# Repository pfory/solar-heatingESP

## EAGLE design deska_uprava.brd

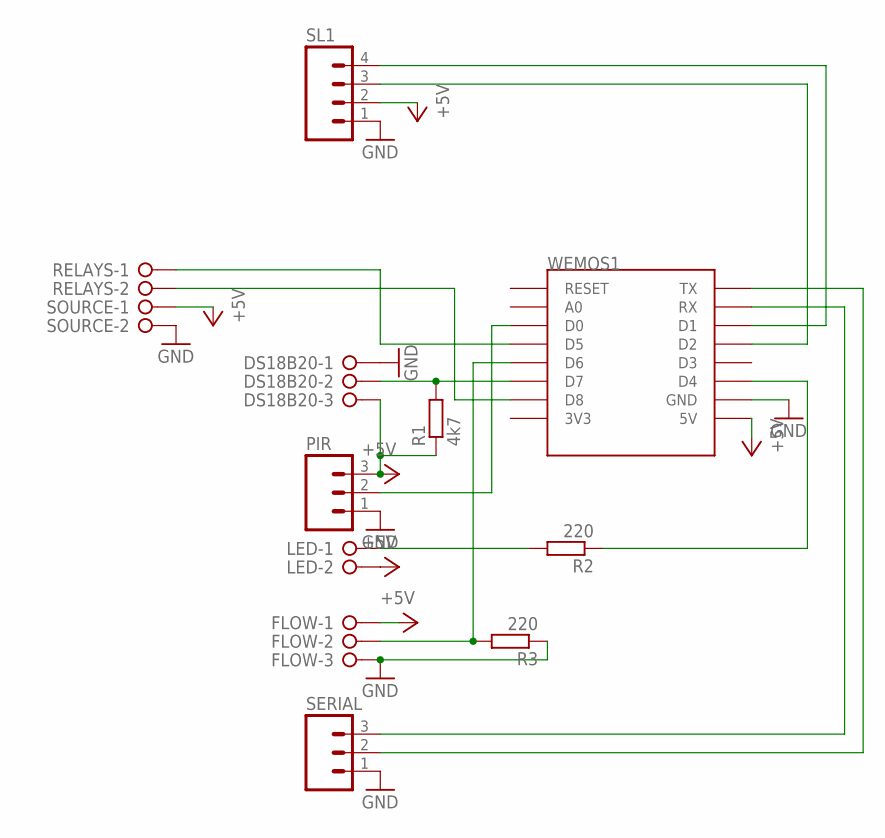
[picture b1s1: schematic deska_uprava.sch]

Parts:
DS18B20: W237-03P; W237-133
FLOW: W237-03P; W237-133
LED: W237-02P; W237-132
PIR: M03; 03P
R1: 4k7; 0207/10
R2, R3: 220; 0207/10
RELAYS: W237-02P; W237-132
SERIAL: M03; 03P
SL1: M04; 04P
SOURCE: W237-02P; W237-132
WEMOS1: WEMOS-D1-MINI

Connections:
+5V: DS18B20.3, FLOW.1, LED.2, PIR.3, R1.1, SL1.2, SOURCE.1, WEMOS1.5V
GND: DS18B20.1, FLOW.3, PIR.1, R3.1, SERIAL.1, SL1.1, SOURCE.2, WEMOS1.GND
unnamed: SERIAL.2, WEMOS1.TX
unnamed: SERIAL.3, WEMOS1.RX
unnamed: SL1.4, WEMOS1.D1
unnamed: SL1.3, WEMOS1.D2
unnamed: PIR.2, WEMOS1.D0
unnamed: R2.1, WEMOS1.D4
unnamed: RELAYS.1, WEMOS1.D5
unnamed: RELAYS.2, WEMOS1.D8
unnamed: DS18B20.2, R1.2, WEMOS1.D7
unnamed: FLOW.2, R3.2, WEMOS1.D6
unnamed: LED.1, R2.2

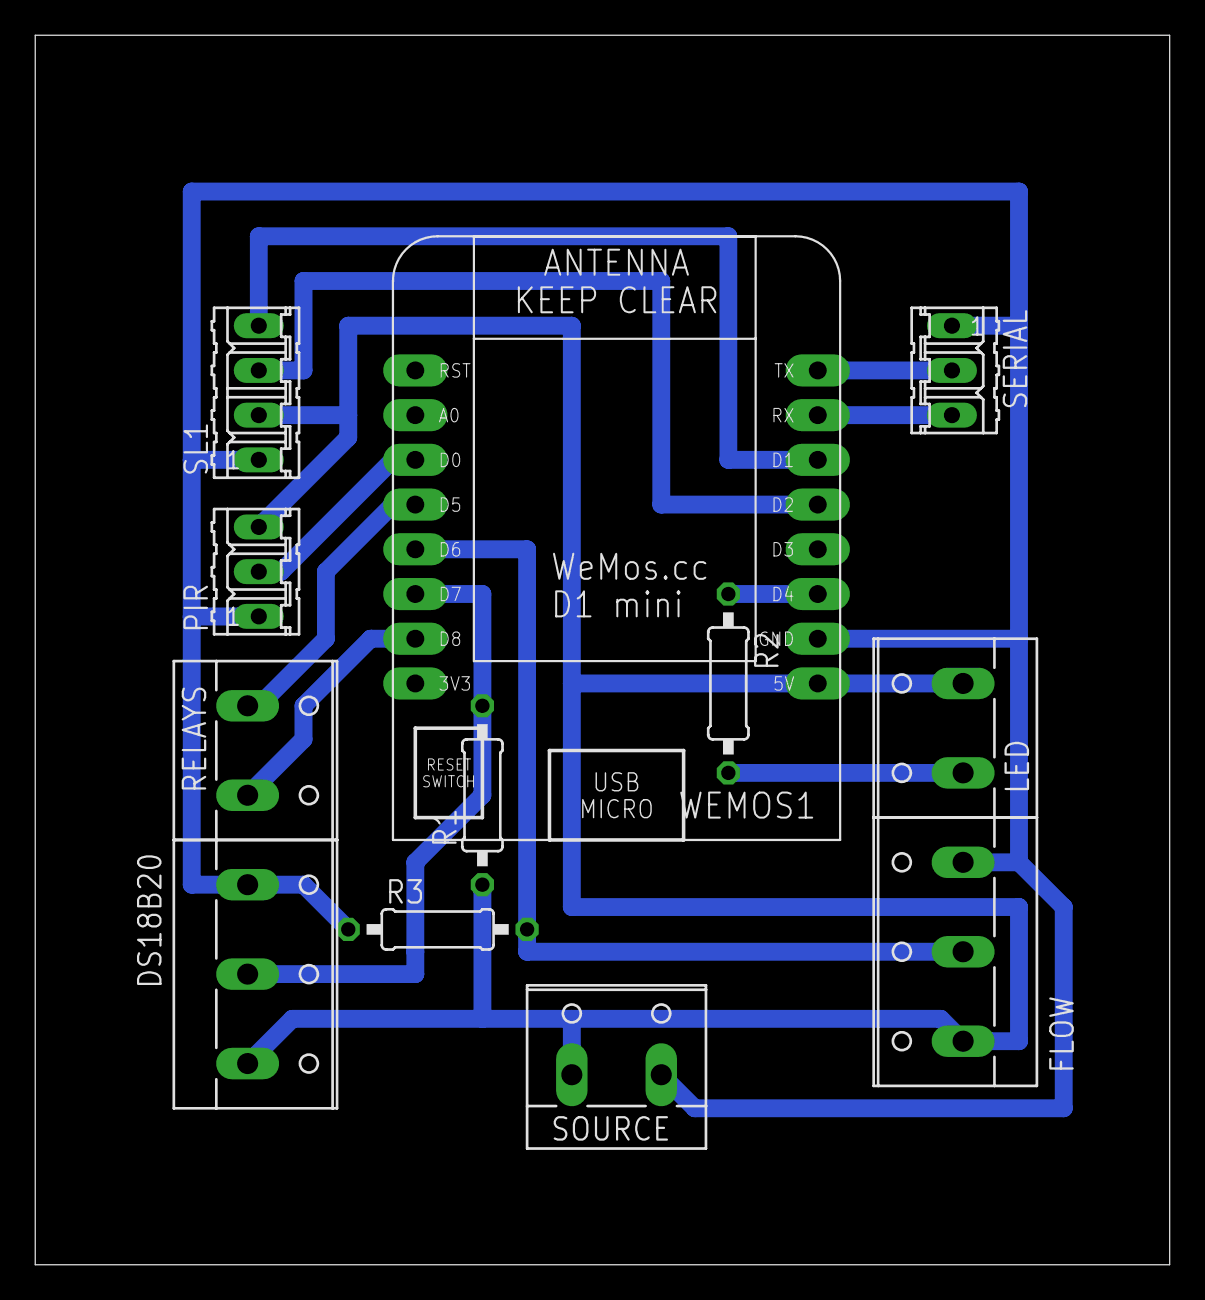
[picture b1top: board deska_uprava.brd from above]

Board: 2 copper layers, 64.4 x 69.8 mm, 12 parts (0 on the bottom side), 13 nets.

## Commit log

2019-01-21 init
2019-01-25 clean up
2019-01-31 sensor order via MQTT
2019-01-31 + deska
2019-02-06 1.52
2019-02-06 +http server page
2019-02-07 +flow
2019-02-07 1.53 change sensor order in code - temporary
2019-02-07 board editing
2019-02-08 flow
2019-02-14 zmena pinu rele
2019-02-15 upravena deska
2019-02-15 + zobrazení úhlu slunce na displeji
2019-02-19 prodleva po sepnuti rele aby se zabranilo cyklickemu spinani
2019-02-20 oprava popisu pinu rele
2019-02-21 uprava mazani displeje
2019-03-03 oprava zobrazovni textu Bez slunce...
2019-03-04 json verze 6
2019-03-07 kosmetika
2019-03-07 -sender
2019-05-16 - oprava snimani prutoku
2019-08-06 v1.60
2019-10-03 +upravy kodu
2019-10-07 0,70
2019-10-07 0.71
2019-10-07 nulovani displeje
2019-10-07 oprava zobrazeni hodin na displeji
2019-10-08 vypis sort orderu pres mqtt zakazani preruseni pred odesilanim mqtt
2019-10-09 1.72
2019-10-09 1.72 opravena chybka
2019-10-09 1.73
2019-10-09 oprava zobrazeni minut behu na displeji
2019-10-10 oprava chyb
2019-10-11 pri chybe teplomeru reset sbernice dallas
2019-10-16 1.00
2019-10-17 rele po startu na ON
2019-10-18 uprava podminky pro reset sbernice
2019-10-18 detaily
2019-10-30 zmena popisu na Naklon
2019-11-01 + posilani tControl + oprava zobrazeni stavu MOF a MON na displeji 1.75
2019-11-05 oprava uhlu slunce
2019-11-11 + uhly pro 11 a 12 mesic
2019-12-25 posilani rssi jednou za 10 minut
2020-03-09 zmena manualniho rizeni
2020-03-09 verze
2020-03-12 1.77 - nastaveni teploty pro rezim room na 40 stupnu natvrdo
2020-03-12 nastaveni teloty v config
2020-03-26 spinani na zaklade i vystupnich teplot - ftp server
2020-09-21 + double reset detector + timeouty pro wifimanager
2020-09-21 uprava ota
2020-09-21 wifimanager a doublereset
2020-09-24 downgrade library wifimanager to 0.15 and build
2020-09-24 web interface
2020-11-05 1.83
2020-12-12 1.91 - vylepseno fungovani bez pripojeni k WiFi
2020-12-14 1.94 - vyřešen problém s označením pinů, nevím proč tam nemůže být Dx jako předtím ale GPIxx
2020-12-15 1.95 - problém s piny vyřešen, použita nesprávnbá deska pro překlad, musí být Wemos d1 r2 mini
2020-12-15 1.95 - ještě drobné úpravy v popisu
2020-12-17 odstraneni duplicit v include
2021-12-02 v2.00
2021-12-08 v2.21
2021-12-08 v2.22
2021-12-08 2.23 je potrebne subscribe
2021-12-08 2.25
2021-12-08 2.26 doplneni chybejici publikací
2021-12-12 2.28
2022-03-28 2.29 - pri sepnuti rele posila informaci o prutoku
2022-04-12 cidla podle serioveho cisla
2022-06-21 2.35
2022-06-21 prohozeni cidel bojler in a bojler out
2022-12-26 filtr nesmyslných teplot
